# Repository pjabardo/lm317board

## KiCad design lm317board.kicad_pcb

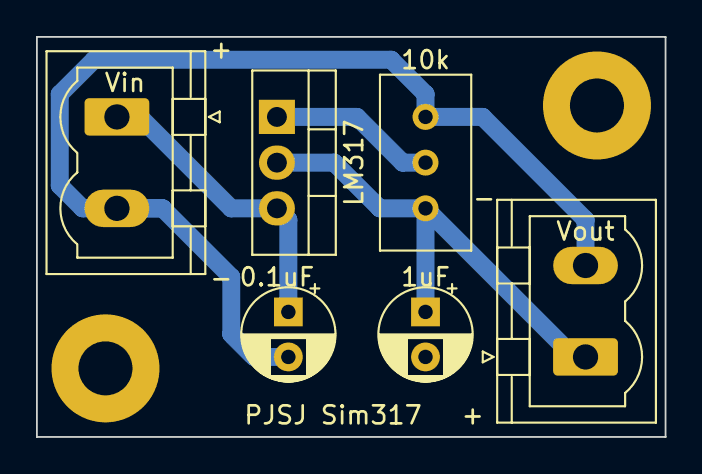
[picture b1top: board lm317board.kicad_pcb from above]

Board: 2 copper layers, 34.9 x 22.2 mm, 8 parts (0 on the bottom side), 4 nets.

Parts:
0.1uF: 0.1 uF; CP_Radial_D5.0mm_P2.50mm
1uF: 1 uF; CP_Radial_D5.0mm_P2.50mm
10k: 10k; Potentiometer_Bourns_3296W_Vertical
 : MountingHole_3mm_Pad
 #2: MountingHole_3mm_Pad
LM317: LM317_TO-220; TO-220-3_Vertical
Vin: Conn_01x02; PhoenixContact_MSTBVA_2,5_2-G-5,08_1x02_P5.08mm_Vertical
Vout: Conn_01x02; PhoenixContact_MSTBVA_2,5_2-G-5,08_1x02_P5.08mm_Vertical

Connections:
/Vout: 1uF.1, 10k.3, LM317.2 (VO), Vout.1
GND: 0.1uF.2, 1uF.2, 10k.1, Vin.2, Vout.2
unnamed: 10k.2, LM317.1 (ADJ)
VCC: 0.1uF.1, LM317.3 (VI), Vin.1

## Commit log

2024-04-12 Initial commit of lm317board
    This is KiCad project for a simple board that uses the IC LM317 to regulate voltage.
